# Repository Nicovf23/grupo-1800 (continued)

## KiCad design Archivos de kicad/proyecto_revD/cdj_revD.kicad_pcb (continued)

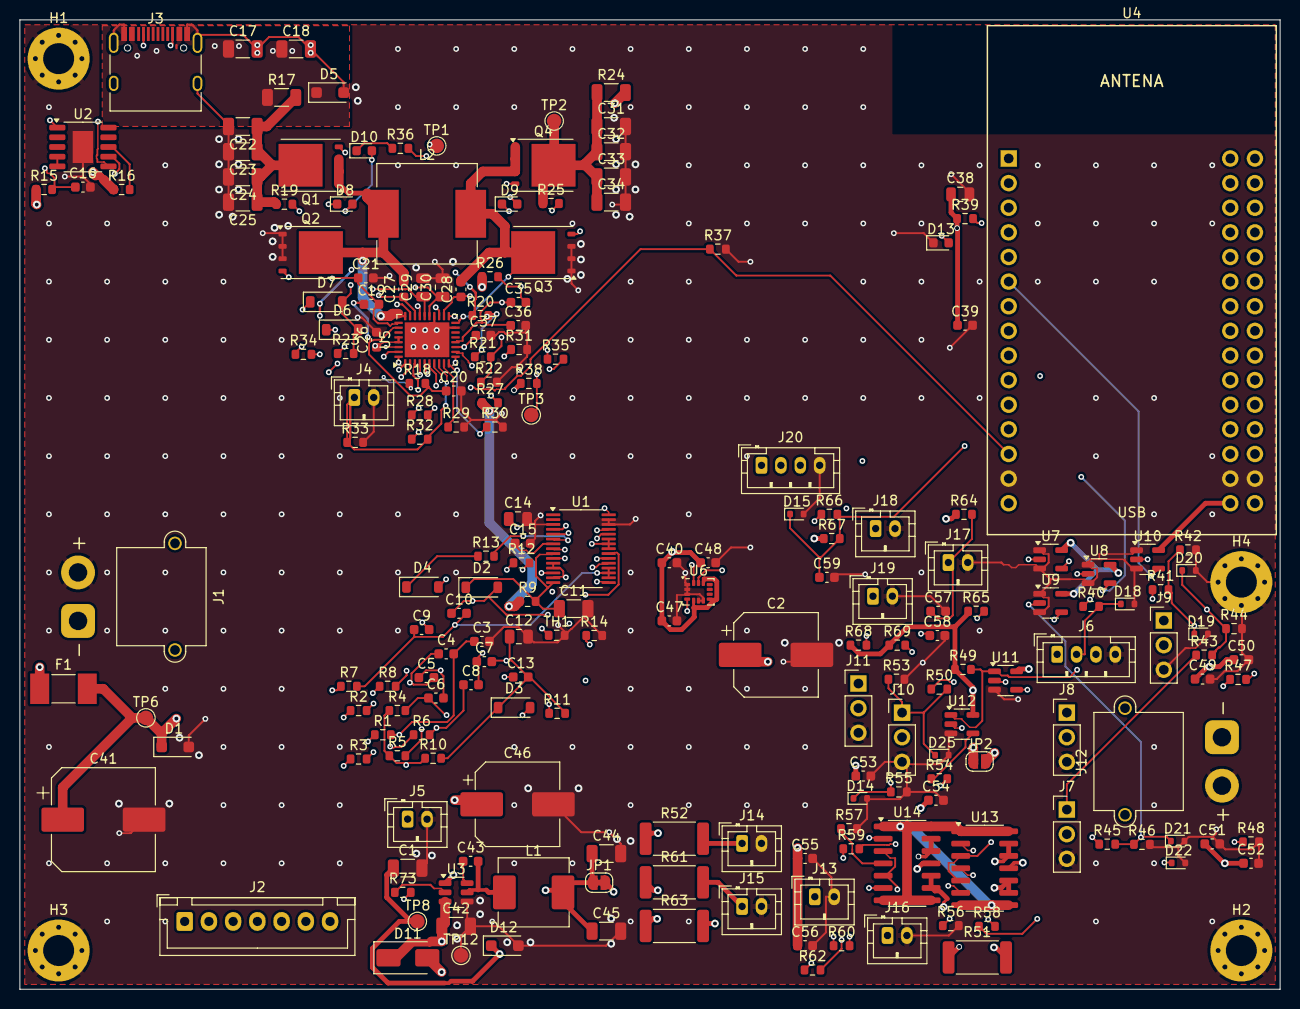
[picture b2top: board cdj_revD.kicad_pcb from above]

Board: 4 copper layers, 130.0 x 100.0 mm, 204 parts (0 on the bottom side), 125 nets.

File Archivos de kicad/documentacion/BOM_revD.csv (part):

Categoria,Referencias,Cant,Valor,Fabricante / N. parte,Encapsulado,Funcion
A,C41,1,220uF 50V,Aluminio 220uF/50V,CP_Elec_10x10.5,Bulk bateria
A,C42,1,10uF 50V,X5R 1206 50V,C_1206_3216Metric,C1 datasheet (10uF)
A,C43,1,100nF,X7R 0603 25V,C_0603_1608Metric,C3 BST (100nF)
A,C44 C45,2,22uF 16V,X5R 1206 16V,C_1206_3216Metric,C2 datasheet (2x22uF)
A,C46,1,100uF 50V,Aluminio 100uF/50V,CP_Elec_8x10.5,Bulk entrada buck
A,D11,1,MBRA340T3G,onsemi MBRA340T3G,D_SMA,Proteccion polaridad inversa logica
A,D12,1,SMF3.3A,Littelfuse SMF3.3A (verificar sufijo),D_SOD-123F,TVS riel 3.3V
A,D14 D15 D18 D19 D20 D21 D22 D25,8,ESD5Z3.3T,onsemi ESD5Z3.3T1G,D_SOD-523,ESD linea expuesta
A,D5,1,SMF24CA,Littelfuse SMF24CA,D_SOD-123F,TVS VBUS (PD 20V < 24V VRWM)
A,JP1,1,3V3,Puente soldadura (cerrado),SolderJumper-2_P1.3mm_Bridged_RoundedPad1.0x1.5mm,Abrir para medir consumo / aislar 3.3V
A,L1,1,4.7uH,"APV APH0630T4R7M (4.7uH, Isat 8-9A, DCR 33mOhm max)",L_APV_APH0630,"Inductor 3.3V: rizado 26-28% (Eq.7), Ipico 2.28A; mejor eficiencia a carga ligera"
A,R73,1,0,1% 0603,R_0603_1608Metric,0R: EN del buck (DNP = placa apagada)
A,TP12,1,GND,Pad de prueba,TestPoint_Pad_D1.5mm,Punto de prueba
A,TP6,1,VBAT,Pad de prueba,TestPoint_Pad_D1.5mm,Punto de prueba
A,TP8,1,+3V3,Pad de prueba,TestPoint_Pad_D1.5mm,Punto de prueba
A,U13 U14,2,BTS723GW,Infineon BTS723GWXUMA1,SOIC-14_3.9x8.7mm_P1.27mm,Interruptor high-side 2 canales con diagnostico
A,U3,1,AP63203WU-7,Diodes AP63203WU-7,TSOT-23-6,3.3V 2A desde bateria
B,C1,1,47uF 10V,X5R 1206 10V,C_1206_3216Metric,Bulk junto al ESP32 (picos WiFi)
B,C2,1,470uF 16V,Aluminio 470uF/16V low-ESR,CP_Elec_8x10.5,Bulk servo (C2 profesor: valor adaptado)
B,D1,1,SMF26CA,Littelfuse SMF26CA,D_SOD-123F,TVS bateria (6S 25.2V < 26V VRWM; SMF24CA no sirve a 6S)
B,D4 D6 D7,3,1N5819HW,Diodes 1N5819HW-7-F,D_SOD-123,Pulso de arranque TS1 (aislado del GPIO)
B,R51,1,1.1k,2512 1W (1 LED a 6S: 0.45W; 0R si el modulo trae R),R_2512_6332Metric,Limitadora LED
B,R52,1,1.2k,2512 1W (1 LED a 6S: 0.45W; 0R si el modulo trae R),R_2512_6332Metric,Limitadora LED
C,C11,1,10uF 50V,X7R 1206 50V,C_1206_3216Metric,Cf BAT (typ 10uF)
C,C12,1,10uF 25V,X7R 0805 25V,C_0805_2012Metric,Cf VC5X
C,C14,1,4.7uF,X7R 0805 10V,C_0805_2012Metric,REGOUT (1-4.7uF)
C,C15 C16 C48,3,1uF,X7R 0603,C_0603_1608Metric,CAP1 1uF
C,C17 C18,2,10uF 35V,X5R 1206 35V,C_1206_3216Metric,
C,C19 C35,2,470nF,X7R 0603 50V,C_0603_1608Metric,
C,C20 C21 C36 C37,4,100nF,X7R 0603 50V,C_0603_1608Metric,
C,C22 C23 C24 C25 C31 C32 C33 C34,8,10uF 50V,X5R 1206 50V,C_1206_3216Metric,Entrada puente (TI 80uF)
C,C26,1,1uF 50V,X7R 0603 50V,C_0603_1608Metric,VAC 1uF
C,C27 C28,2,100nF,X7R 0603 25V,C_0603_1608Metric,Bootstrap 1
C,C29 C30,2,4.7uF,X7R 0805 16V,C_0805_2012Metric,
C,C10 C13 C3 C4 C5 C6 C7 C8 C9,9,1uF,X7R 0603 25V,C_0603_1608Metric,Filtro celda Cc (typ 1uF)
C,C38,1,22uF,X5R 0805 10V,C_0805_2012Metric,Desacoplo 3V3 junto al zocalo
C,C39 C40 C47 C49 C50 C51 C52 C53 C54 C57 C58 C59,12,100nF,X7R 0603,C_0603_1608Metric,
C,C55 C56,2,100nF 50V,X7R 0603 50V,C_0603_1608Metric,
C,D10,1,AZUL PG,LED 0603,LED_0603_1608Metric,Indicador cargador
C,D13,1,VERDE 3V3,LED verde 0603,LED_0603_1608Metric,
C,D2 D3,2,1N4148W,Diodes 1N4148W-7-F,D_SOD-123,Diodo entrada superior -> BAT (9.1.3)
C,D8,1,NARANJA STAT1,LED 0603,LED_0603_1608Metric,Indicador cargador
C,D9,1,VERDE STAT2,LED 0603,LED_0603_1608Metric,Indicador cargador
C,F1,1,5A,"Littelfuse 0451005.MRL (5A, verificar Vr>=32V)",Fuse_Littelfuse-NANO2-451_453,Sobrecorriente placa+cargador
C,H1 H2 H3 H4,4,M3,M3 + arandela antivibracion,MountingHole_3.2mm_M3_Pad_Via,
C,J1,1,BATERIA 6S (XT30),AMASS XT30PW-M,AMASS_XT30PW-M_1x02_P2.50mm_Horizontal,Toma de bateria en paralelo con el ESC
C,J10,1,ESC,Header 1x03 2.54mm,PinHeader_1x03_P2.54mm_Vertical,
C,J11,1,SERVO,Header 1x03 2.54mm,PinHeader_1x03_P2.54mm_Vertical,
C,J12,1,VSERVO IN (BEC),AMASS XT30PW-M,AMASS_XT30PW-M_1x02_P2.50mm_Horizontal,
C,J13,1,LUZ blancas delanteras,JST B2B-PH-K-S,JST_PH_B2B-PH-K_1x02_P2.00mm_Vertical,
C,J14,1,LUZ rojas traseras,JST B2B-PH-K-S,JST_PH_B2B-PH-K_1x02_P2.00mm_Vertical,
C,J15,1,LUZ rojas Modo Sport,JST B2B-PH-K-S,JST_PH_B2B-PH-K_1x02_P2.00mm_Vertical,
C,J16,1,LUZ freno/aux,JST B2B-PH-K-S,JST_PH_B2B-PH-K_1x02_P2.00mm_Vertical,
C,J17,1,NTC MOTOR 10k,JST B2B-PH-K-S,JST_PH_B2B-PH-K_1x02_P2.00mm_Vertical,
C,J18,1,NTC ESC 10k,JST B2B-PH-K-S,JST_PH_B2B-PH-K_1x02_P2.00mm_Vertical,
C,J19,1,BOTON AUTORIZ. SPORT,JST B2B-PH-K-S,JST_PH_B2B-PH-K_1x02_P2.00mm_Vertical,
C,J2,1,BALANCEO 6S (JST-XH),JST B7B-XH-A,JST_XH_B7B-XH-A_1x07_P2.50mm_Vertical,Conector de balanceo de la LiPo 6S
C,J20,1,I2C EXP,JST B4B-PH-K-S,JST_PH_B4B-PH-K_1x04_P2.00mm_Vertical,
C,J3,1,USB-C (SOLO CARGA),HRO TYPE-C-31-M-12,USB_C_Receptacle_HRO_TYPE-C-31-M-12,Entrada de carga PD
C,J4,1,NTC BATERIA 10k (103AT),JST B2B-PH-K-S,JST_PH_B2B-PH-K_1x02_P2.00mm_Vertical,NTC pegado a la LiPo: sin NTC no carga
C,J5,1,INTERRUPTOR (abierto=ON),JST B2B-PH-K-S,JST_PH_B2B-PH-K_1x02_P2.00mm_Vertical,Interruptor de electronica en chasis
C,J6,1,RX SERIE (CRSF/SBUS/iBUS),JST B4B-PH-K-S,JST_PH_B4B-PH-K_1x04_P2.00mm_Vertical,
C,J7,1,RC_CH1 PWM,Header 1x03 2.54mm,PinHeader_1x03_P2.54mm_Vertical,
C,J8,1,RC_CH2 PWM,Header 1x03 2.54mm,PinHeader_1x03_P2.54mm_Vertical,
C,J9,1,RC_CH3 PWM,Header 1x03 2.54mm,PinHeader_1x03_P2.54mm_Vertical,
C,JP2,1,BEC ESC->VSERVO,Puente soldadura (abierto),SolderJumper-2_P1.3mm_Open_RoundedPad1.0x1.5mm,
C,L2,1,10uH,"Vishay IHLP4040DZER100M5A (LCSC C511353; 10uH, 6.5A, DCR 30.9mOhm)",L_Vishay_IHLP-4040,Inductor buck-boost 250kHz (reducido 2026-11-05)
C,Q1 Q2 Q3 Q4,4,BSC028N06LS3,"Infineon BSC028N06LS3 (60V 2.8mOhm, logic level)",TDSON-8-1,Puente buck-boost
C,R1 R10 R2 R3 R4 R5 R50 R54 R6 R7 R8 R9,12,100,1% 0603,R_0603_1608Metric,Filtro entrada celda Rc (typ 100R)
C,R11 R16 R37 R38 R49 R53 R55 R64 R65 R67,10,10k,1% 0603,R_0603_1608Metric,TS2 sin NTC: 10k a VC5X (Tabla 9-1)
C,R12 R13 R15 R41 R43 R45 R47 R66,8,1k,1% 0603,R_0603_1608Metric,Serie boot
C,R14 R20,2,1M,1% 0603,R_0603_1608Metric,RALERT 1M a VSS
C,R17 R24,2,5m,Shunt 5mOhm 1206 1W,R_1206_3216Metric,RAC_SNS
C,R18 R19 R23 R25 R26,5,10,1% 0603,R_0603_1608Metric,
C,R21,1,261k,1% 0603,R_0603_1608Metric,RAC2
C,R22,1,73.2k,1% 0603,R_0603_1608Metric,RAC3
C,R27,1,249k,1% 0603,R_0603_1608Metric,FB RTOP (TI 249k)
C,R28,1,16.2k,1% 0603,R_0603_1608Metric,FB RBOT: 25.14V = 4.19V/celda
C,R29,1,24.9k,1% 0603,R_0603_1608Metric,ICHG = 50AkOhm/24.9k = 2.0A
C,R30,1,6.65k,1% 0603,R_0603_1608Metric,ILIM = 20AkOhm/6.65k = 3.0A (60W)
C,R31,1,133k,1% 0603,R_0603_1608Metric,fsw 250kHz (Tabla 6-2)
C,R32,1,5.23k,1% 0603,R_0603_1608Metric,TS RT1 (TI 5.24k)
C,R33,1,30.1k,1% 0603,R_0603_1608Metric,TS RT2 (TI 30.31k)
C,R34 R35 R36 R39 R58 R59 R60 R62,8,2.2k,1% 0603,R_0603_1608Metric,
C,R40,1,220,1% 0603,R_0603_1608Metric,
C,R42 R44 R46 R48,4,100k,1% 0603,R_0603_1608Metric,
C,R56 R57,2,150,1% 0603,R_0603_1608Metric,"GND logico (proteccion inversion, datasheet)"
C,R61 R63,2,1.2k,2512 1W (1 LED a 6S: 0.45W; 0R si el modulo trae R),R_2512_6332Metric,Limitadora LED
C,R68 R69,2,4.7k,1% 0603,R_0603_1608Metric,
C,TH1,1,10k 3435K,Murata NCP18XH103F03RB,R_0603_1608Metric,TS1 temperatura placa (obligatorio)
C,TP1,1,VBUS,Pad de prueba,TestPoint_Pad_D1.5mm,Punto de prueba
C,TP2,1,CHG_VOUT,Pad de prueba,TestPoint_Pad_D1.5mm,Punto de prueba
C,TP3,1,CHG_INT,Pad de prueba,TestPoint_Pad_D1.5mm,Punto de prueba
C,U1,1,BQ7693002DBT,"TI BQ7693002DBTR (REGOUT 3.3V, I2C 0x08, sin CRC; LCSC C2871830)",TSSOP-30_4.4x7.8mm_P0.5mm,Medicion por celda y balanceo 6S
C,U2,1,CH224K,WCH CH224K (LCSC C970725),SSOP-10-1EP_3.9x4.9mm_P1mm_EP2.1x3.3mm,"Negocia 20V PD (CFG1 NC=20V, DP-DM unidos: solo PD)"
C,U4,1,ESP32 DevKit V1 (30p),DOIT ESP32 DevKit V1 30 pines + 2x tira hembra 1x15 2.54mm,ESP32_DevKit_V1_30P,MCU en zocalo
C,U5,1,BQ25756,TI BQ25756RRVR (LCSC C19272232),QFN-36-1EP_5x6mm_P0.5mm_EP3.6x4.6mm,Controlador cargador buck-boost 1-14S
C,U6,1,LSM6DSL,ST LSM6DSLTR,LGA-14_3x2.5mm_P0.5mm_LayoutBorder3x4y,IMU 6 ejes por I2C (0x6A)
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
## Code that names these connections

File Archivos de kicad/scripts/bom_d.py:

import sys, csv, collections; sys.path.insert(0, "."); import design_d as D
rows = collections.OrderedDict()
for p in D.P:
    if p["ref"].startswith("#"): continue
    r = rows.setdefault((p["cat"], p["value"], p["fp"], p["mpn"]), dict(refs=[], fn=p["fn"])); r["refs"].append(p["ref"])
with open("revD/BOM_revD.csv", "w", newline="", encoding="utf-8-sig") as f:
    w = csv.writer(f); w.writerow(["Categoria", "Referencias", "Cant", "Valor", "Fabricante / N. parte", "Encapsulado", "Funcion"])
    for (cat, val, fp, mpn), r in sorted(rows.items(), key=lambda kv: (kv[0][0], kv[1]["refs"][0])):
        w.writerow([cat, " ".join(sorted(r["refs"])), len(r["refs"]), val, mpn, fp.split(":")[-1], r["fn"]])
dk = next(p for p in D.P if p["sym"] == "ESP32_DevKit_V1")
names = {"1": "EN", "2": "VP/GPIO36", "3": "VN/GPIO39", "4": "GPIO34", "5": "GPIO35", "6": "GPIO32", "7": "GPIO33", "8": "GPIO25", "9": "GPIO26", "10": "GPIO27",
         "11": "GPIO14", "12": "GPIO12", "13": "GPIO13", "14": "GND", "15": "VIN", "16": "GPIO23", "17": "GPIO22", "18": "TX0/GPIO1", "19": "RX0/GPIO3", "20": "GPIO21",
         "21": "GPIO19", "22": "GPIO18", "23": "GPIO5", "24": "TX2/GPIO17", "25": "RX2/GPIO16", "26": "GPIO4", "27": "GPIO2", "28": "GPIO15", "29": "GND", "30": "3V3"}
with open("revD/PINES_DEVKIT_revD.csv", "w", newline="", encoding="utf-8-sig") as f:
    w = csv.writer(f); w.writerow(["Pin zocalo", "Lado", "Pin DevKit", "Senal"])
    for n in map(str, range(1, 31)):
        w.writerow([n, "izquierdo" if int(n) <= 15 else "derecho", names[n], dk["pins"].get(n, "libre (NC)")])
c = collections.Counter(p["cat"] for p in D.P if not p["ref"].startswith("#"))
print("BOM:", len(rows), "lineas,", sum(c.values()), "piezas", dict(sorted(c.items())))

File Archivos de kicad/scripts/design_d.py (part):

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C("C71b", "4.7uF", "AFE_REGOUT", "GND", B, C0805, "X7R 0805 10V", fn="REGOUT (1-4.7uF)")
C("C72b", "1uF", "AFE_CAP1", "GND", B, fn="CAP1 1uF")
add("TH1", "Device", "Thermistor_NTC", "10k 3435K", "Resistor_SMD:R_0603_1608Metric", "Murata NCP18XH103F03RB", {"1": "AFE_TS1", "2": "GND"}, B, "C", "TS1 temperatura placa (obligatorio)")
add("D11", "Device", "D_Schottky", "1N5819HW", SOD123, "Diodes 1N5819HW-7-F", {"1": "AFE_BOOT_K", "2": "AFE_BOOT_A"}, B, "B", "Pulso de arranque TS1 (aislado del GPIO)")
R("R66", "1k", "AFE_BOOT", "AFE_BOOT_A", B, fn="Serie boot")
R("R67", "1k", "AFE_BOOT_K", "AFE_TS1", B, fn="Serie boot")
R("R59", "1M", "AFE_ALERT", "GND", B, fn="RALERT 1M a VSS")
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R("R85", "6.65k", "CHG_ILIM", "GND", B, fn="ILIM = 20AkOhm/6.65k = 3.0A (60W)")
R("R86", "133k", "CHG_FSW", "GND", B, fn="fsw 250kHz (Tabla 6-2)")
R("R87", "5.23k", "CHG_REGN", "CHG_TS", B, fn="TS RT1 (TI 5.24k)"); R("R88", "30.1k", "CHG_TS", "GND", B, fn="TS RT2 (TI 30.31k)")
add("J4", "Connector_Generic", "Conn_01x02", "NTC BATERIA 10k (103AT)", PH2, "JST B2B-PH-K-S", {"1": "CHG_TS", "2": "GND"}, B, "C", "NTC pegado a la LiPo: sin NTC no carga")
for k, (net, col) in enumerate([("CHG_STAT1", "NARANJA STAT1"), ("CHG_STAT2", "VERDE STAT2"), ("CHG_PG", "AZUL PG")]):
    add(f"D{29+k}", "Device", "LED", col, LED0603, "LED 0603", {"2": "CHG_REGN", "1": f"{net}_K"}, B, "C", "Indicador cargador")
    R(f"R{89+k}", "2.2k", f"{net}_K", net, B)
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add("D15", "Device", "D_Zener", "SMF3.3A", SOD123F, "Littelfuse SMF3.3A (verificar sufijo)", {"1": "+3V3", "2": "GND"}, B, "A", "TVS riel 3.3V")
C("C1", "47uF 10V", "+3V3", "GND", B, C1206, "X5R 1206 10V", "B", "Bulk junto al ESP32 (picos WiFi)")
R("R73", "0", "BUCK_EN", "PWR_SW", B, cat="A", fn="0R: EN del buck (DNP = placa apagada)")
add("J5", "Connector_Generic", "Conn_01x02", "INTERRUPTOR (abierto=ON)", PH2, "JST B2B-PH-K-S", {"1": "PWR_SW", "2": "GND"}, B, "C", "Interruptor de electronica en chasis")
TPt("TP8", "+3V3", B, "A"); TPt("TP12", "GND", B, "A")

# ======================= 5. ESP32 DevKit V1 (DOIT, 30 pines, en zocalo) =======================
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
# ======================= 7. RECEPTOR RC (alimentado por BEC) =======================
B = "RC"
add("J7", "Connector_Generic", "Conn_01x04", "RX SERIE (CRSF/SBUS/iBUS)", PH4, "JST B4B-PH-K-S", {"1": "VSERVO", "2": "RC_TX_OUT", "3": "RC_RX_IN", "4": "GND"}, B)
R("R14", "220", "RC_TX", "RC_TX_OUT", B); ESD("D18", "RC_TX_OUT", B)
for j, sig in (("J8", "RC_CH1"), ("J9", "RC_CH2"), ("J10", "RC_CH3")):
    add(j, "Connector_Generic", "Conn_01x03", f"{sig} PWM", HDR3, "Header 1x03 2.54mm", {"1": f"{sig}_IN", "2": "VSERVO", "3": "GND"}, B)
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
# ======================= 10. SENSORES / BOTON SPORT / I2C =======================
B = "AUX"
add("J18", "Connector_Generic", "Conn_01x02", "NTC MOTOR 10k", PH2, "JST B2B-PH-K-S", {"1": "NTC_MOTOR", "2": "GND"}, B)
R("R44", "10k", "+3V3", "NTC_MOTOR", B); C("C31", "100nF", "NTC_MOTOR", "GND", B)
add("J19", "Connector_Generic", "Conn_01x02", "NTC ESC 10k", PH2, "JST B2B-PH-K-S", {"1": "NTC_ESC", "2": "GND"}, B)
R("R45", "10k", "+3V3", "NTC_ESC", B); C("C32", "100nF", "NTC_ESC", "GND", B)
add("J20", "Connector_Generic", "Conn_01x02", "BOTON AUTORIZ. SPORT", PH2, "JST B2B-PH-K-S", {"1": "SPORT_BTN_EXT", "2": "GND"}, B)
R("R46", "1k", "SPORT_BTN_EXT", "SPORT_BTN", B); R("R47", "10k", "+3V3", "SPORT_BTN", B); C("C33", "100nF", "SPORT_BTN", "GND", B)
ESD("D27", "SPORT_BTN", B)
add("J21", "Connector_Generic", "Conn_01x04", "I2C EXP", PH4, "JST B4B-PH-K-S", {"1": "+3V3", "2": "I2C_SDA", "3": "I2C_SCL", "4": "GND"}, B)
R("R48", "4.7k", "+3V3", "I2C_SDA", B); R("R49", "4.7k", "+3V3", "I2C_SCL", B)

# ======================= 11. MECANICO / FLAGS =======================
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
